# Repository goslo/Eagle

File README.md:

# Eagle
 A bunch of PCB designs

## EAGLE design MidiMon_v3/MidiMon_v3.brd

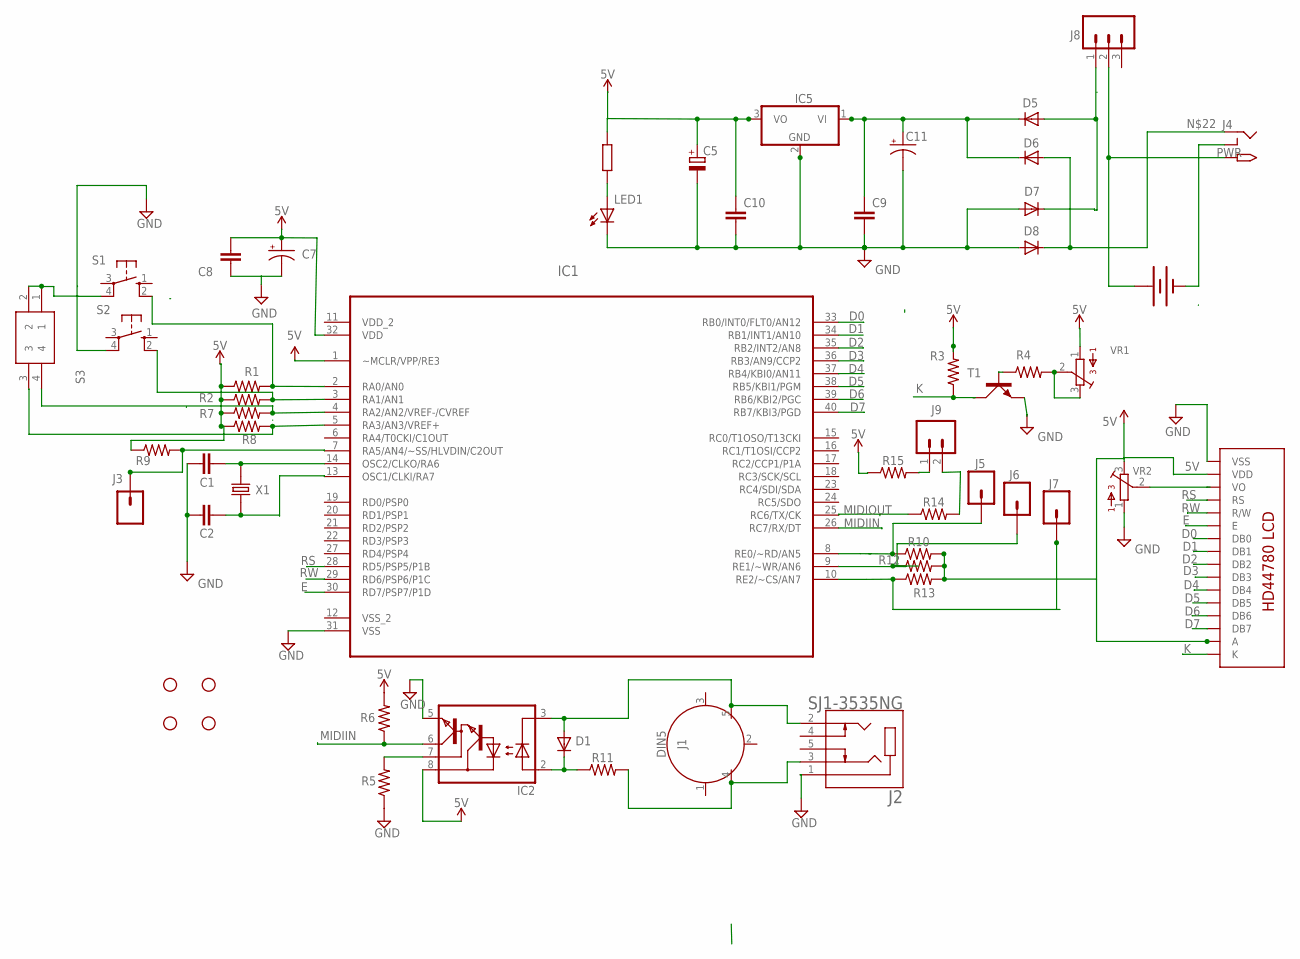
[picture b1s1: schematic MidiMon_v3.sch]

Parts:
BAT1: BATTERY; PP3_BATTERBOX
C1, C2: 33pF; CAP-PTH-2.54
C5: 10uf; E2,5-7
C7: 10uF; CPOL-RADIAL-2.5MM-5MM
C8: 0.1uF; C025-024X044
C9: 330nf; C025-024X044
C10: 100nf; C025-024X044
C11: 2200uf; E5-10,5
D1: DIODEDO-1N4148; DO-1N4148
D5, D6, D7, D8: 1N4004; DO-VERT
H1, H2, H3, H4: STAND-OFFTIGHT; STAND-OFF-TIGHT
IC1: PIC18F4520-I/P; DIP254P1524X533-40
IC2: 6N138; DIL08
IC5: 7805TV; TO220V
J1: DIN5; DIN5-RA-PTH
J2: SJ1-3535NG; CUI_SJ1-3535NG
J3, J5, J6, J7: CONN_01; 1X01
J4: 2.1MMJACKTHM; PJ-102A
J8: CONN_03; 1X03
J9: CONN_02; 1X02
LED1: LED3MM
R1, R2, R3, R7, R8, R9, R10, R12, R13: 10k; AXIAL-0.3
R4: 1k; AXIAL-0.3
R5: 5.6k; AXIAL-0.3
R6: 1.2k; AXIAL-0.3
R11, R14, R15: 220; AXIAL-0.3
R20: 1k; 0207/7
S1, S2: 40-XX; B3F-40XX
S3: 195-2MST; DIPS774W56P254L726H790Q4N
T1: 2N3904; TO92D
U$2: LCD-HD4478020X4-3HOLES; LCD-20X4-3HOLES
VR1, VR2: BOURNS_3362P_TRIMMERP; BOURNS_3362P_TRIMMER
X1: ECS-100-18-4X; XTAL_ECS-100-18-4X

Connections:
5V: C5.+, C7.1 (+), C8.2, C10.1, IC1.1 (~MCLR/VPP/RE3), IC1.32 (VDD), IC2.8 (VCC), IC5.3 (VO), R1.P$1 (1), R2.P$1 (1), R3.P$2 (2), R6.P$2 (2), R7.P$1 (1), R8.P$1 (1), R9.P$1 (1), R10.P$2 (2), R12.P$2 (2), R13.P$2 (2), R15.P$1 (1), R20.1, U$2.P$2 (VDD), U$2.P$15 (A), VR1.1, VR2.3
D0: IC1.33 (RB0/INT0/FLT0/AN12), U$2.P$7 (DB0)
D1: IC1.34 (RB1/INT1/AN10), U$2.P$8 (DB1)
D2: IC1.35 (RB2/INT2/AN8), U$2.P$9 (DB2)
D3: IC1.36 (RB3/AN9/CCP2), U$2.P$10 (DB3)
D4: IC1.37 (RB4/KBI0/AN11), U$2.P$11 (DB4)
D5: IC1.38 (RB5/KBI1/PGM), U$2.P$12 (DB5)
D6: IC1.39 (RB6/KBI2/PGC), U$2.P$13 (DB6)
D7: IC1.40 (RB7/KBI3/PGD), U$2.P$14 (DB7)
E: IC1.30 (RD7/PSP7/P1D), U$2.P$6 (E)
GND: C1.1, C2.1, C5.-, C7.2 (-), C8.1, C9.2, C10.2, C11.-, D7.A, D8.A, IC1.31 (VSS), IC2.5 (GND), IC5.2 (GND), J2.1, LED1.K (C), R5.P$1 (1), S1.4 (P1), S2.4 (P1), S3.1, S3.2, T1.E, U$2.P$1 (VSS), VR2.1
K: R3.P$1 (1), T1.C, U$2.P$16 (K)
MIDIIN: IC1.26 (RC7/RX/DT), IC2.6 (VO), R6.P$1 (1)
unnamed: BAT1.0V (-), J4.RING_SW
unnamed: R4.P$2 (2), VR1.2, VR1.3
unnamed: IC2.7 (VB), R5.P$2 (2)
unnamed: D1.C, IC2.2 (A), R11.P$1 (1)
unnamed: J1.4, J2.3, R11.P$2 (2)
unnamed: D1.A, IC2.3 (C), J1.5, J2.2
unnamed: C1.2, IC1.14 (OSC2/CLKO/RA6), X1.2
unnamed: C2.2, IC1.13 (OSC1/CLKI/RA7), X1.1
unnamed: D5.A, D7.C, J8.1
unnamed: IC1.4 (RA2/AN2/VREF-/CVREF), R7.P$2 (2), S3.4
unnamed: IC1.2 (RA0/AN0), R1.P$2 (2), S1.2 (S1)
unnamed: IC1.3 (RA1/AN1), R2.P$2 (2), S2.2 (S1)
unnamed: IC1.5 (RA3/AN3/VREF+), R8.P$2 (2), S3.3
unnamed: LED1.A, R20.2
unnamed: IC1.7 (RA5/AN4/~SS/HLVDIN/C2OUT), J3.1, R9.P$2 (2)
unnamed: IC1.25 (RC6/TX/CK), R14.P$1 (1)
unnamed: D6.A, D8.C, J4.RING
unnamed: U$2.P$3 (VO), VR2.2
unnamed: R4.P$1 (1), T1.B
unnamed: IC1.9 (RE1/~WR/AN6), J6.1, R12.P$1 (1)
unnamed: IC1.8 (RE0/~RD/AN5), J5.1, R10.P$1 (1)
unnamed: IC1.10 (RE2/~CS/AN7), J7.1, R13.P$1 (1)
unnamed: J9.2, R14.P$2 (2)
unnamed: J9.1, R15.P$2 (2)
PWR: BAT1.9V (+), J4.TIP, J8.2
RS: IC1.28 (RD5/PSP5/P1B), U$2.P$4 (RS)
RW: IC1.29 (RD6/PSP6/P1C), U$2.P$5 (R/W)
VDD_2: IC1.11 (VDD_2)
VIN: C9.1, C11.+, D5.C, D6.C, IC5.1 (VI)
VSS_2: IC1.12 (VSS_2)

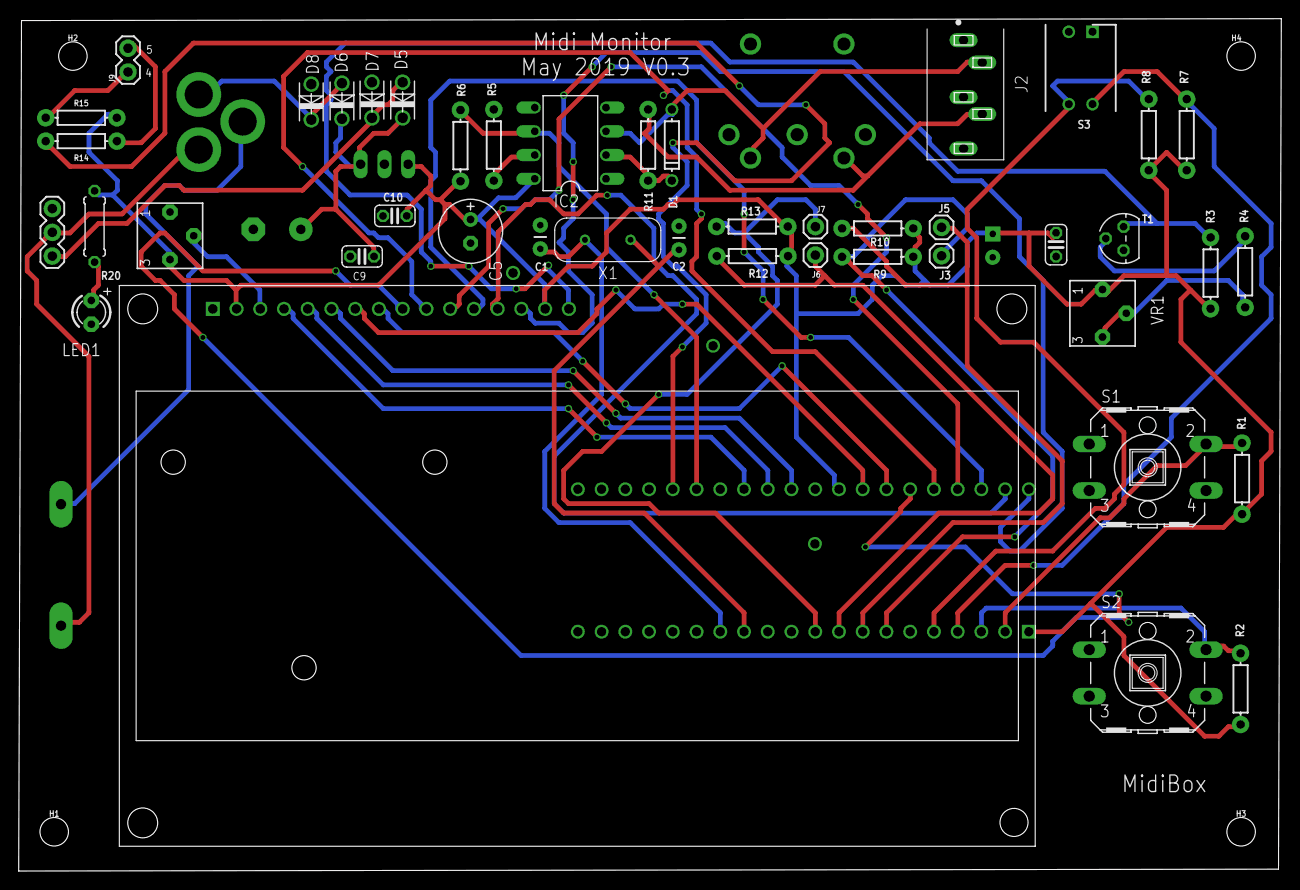
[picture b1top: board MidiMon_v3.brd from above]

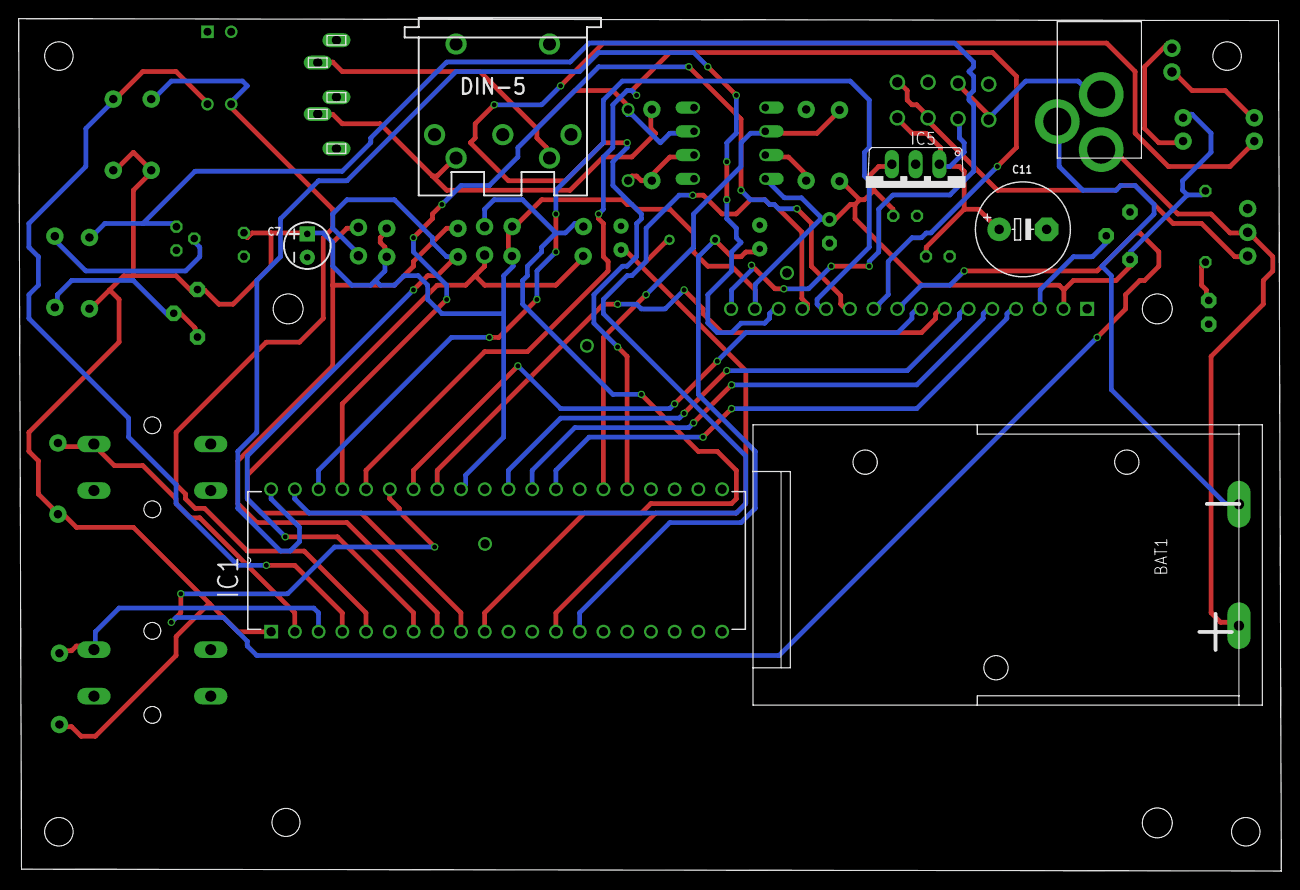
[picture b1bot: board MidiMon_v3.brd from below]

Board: 2 copper layers, 135.1 x 91.2 mm, 55 parts (7 on the bottom side), 41 nets.

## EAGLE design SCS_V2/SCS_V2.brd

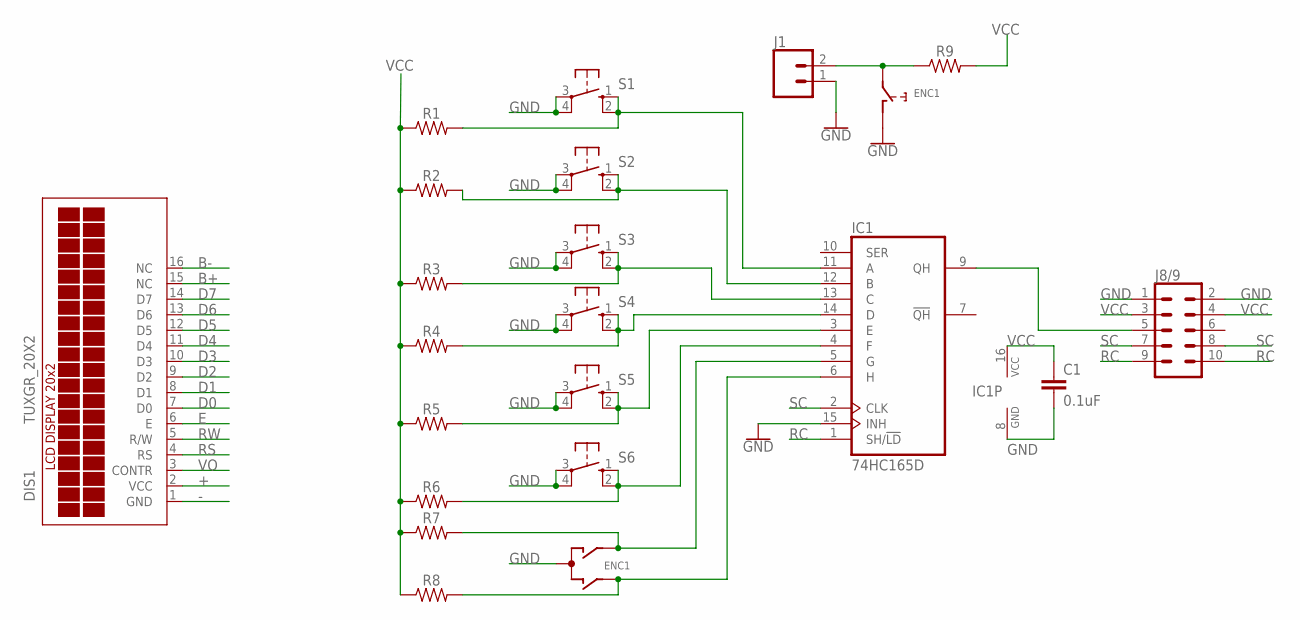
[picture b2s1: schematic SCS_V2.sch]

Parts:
C1: 0.1uF; 0603
DIS1: TUXGR_20X2
ENC1: EC12E_SW; ALPS_EC12E_SW
IC1: 74HC165D; SO16
J1: CONN_02; 1X02
J8/9: CONN_05X2SHD_LOCK; 2X5-SHROUDED_LOCK
R1, R2, R3, R4, R5, R6, R7, R8, R9: 10k; 0603
S1, S2, S3, S4, S5, S6: 40-XX; B3F-40XX

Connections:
+: DIS1.2 (VCC)
-: DIS1.1 (GND)
B+: DIS1.15 (NC)
B-: DIS1.16 (NC)
D0: DIS1.7 (D0)
D1: DIS1.8 (D1)
D2: DIS1.9 (D2)
D3: DIS1.10 (D3)
D4: DIS1.11 (D4)
D5: DIS1.12 (D5)
D6: DIS1.13 (D6)
D7: DIS1.14 (D7)
E: DIS1.6 (E)
GND: C1.2, ENC1.C, ENC1.D (1), IC1.8 (GND), IC1.15 (INH), J1.1, J8/9.1, J8/9.2, S1.3, S1.4 (P1), S2.3, S2.4 (P1), S3.3, S3.4 (P1), S4.3, S4.4 (P1), S5.3, S5.4 (P1), S6.3, S6.4 (P1)
unnamed: IC1.3 (E), R5.2, S5.1 (S), S5.2 (S1)
unnamed: ENC1.A, IC1.5 (G), R7.2
unnamed: IC1.4 (F), R6.2, S6.1 (S), S6.2 (S1)
unnamed: IC1.9 (QH), J8/9.5
unnamed: IC1.14 (D), R4.2, S4.1 (S), S4.2 (S1)
unnamed: IC1.13 (C), R3.2, S3.1 (S), S3.2 (S1)
unnamed: IC1.12 (B), R2.2, S2.1 (S), S2.2 (S1)
unnamed: IC1.11 (A), R1.2, S1.1 (S), S1.2 (S1)
unnamed: ENC1.B, IC1.6 (H), R8.2
unnamed: ENC1.E (2), J1.2, R9.1
RC: IC1.1 (SH/!LD), J8/9.9, J8/9.10
RS: DIS1.4 (RS)
RW: DIS1.5 (R/W)
SC: IC1.2 (CLK), J8/9.7, J8/9.8
VCC: C1.1, IC1.16 (VCC), J8/9.3, J8/9.4, R1.1, R2.1, R3.1, R4.1, R5.1, R6.1, R7.1, R8.1, R9.2
VO: DIS1.3 (CONTR)

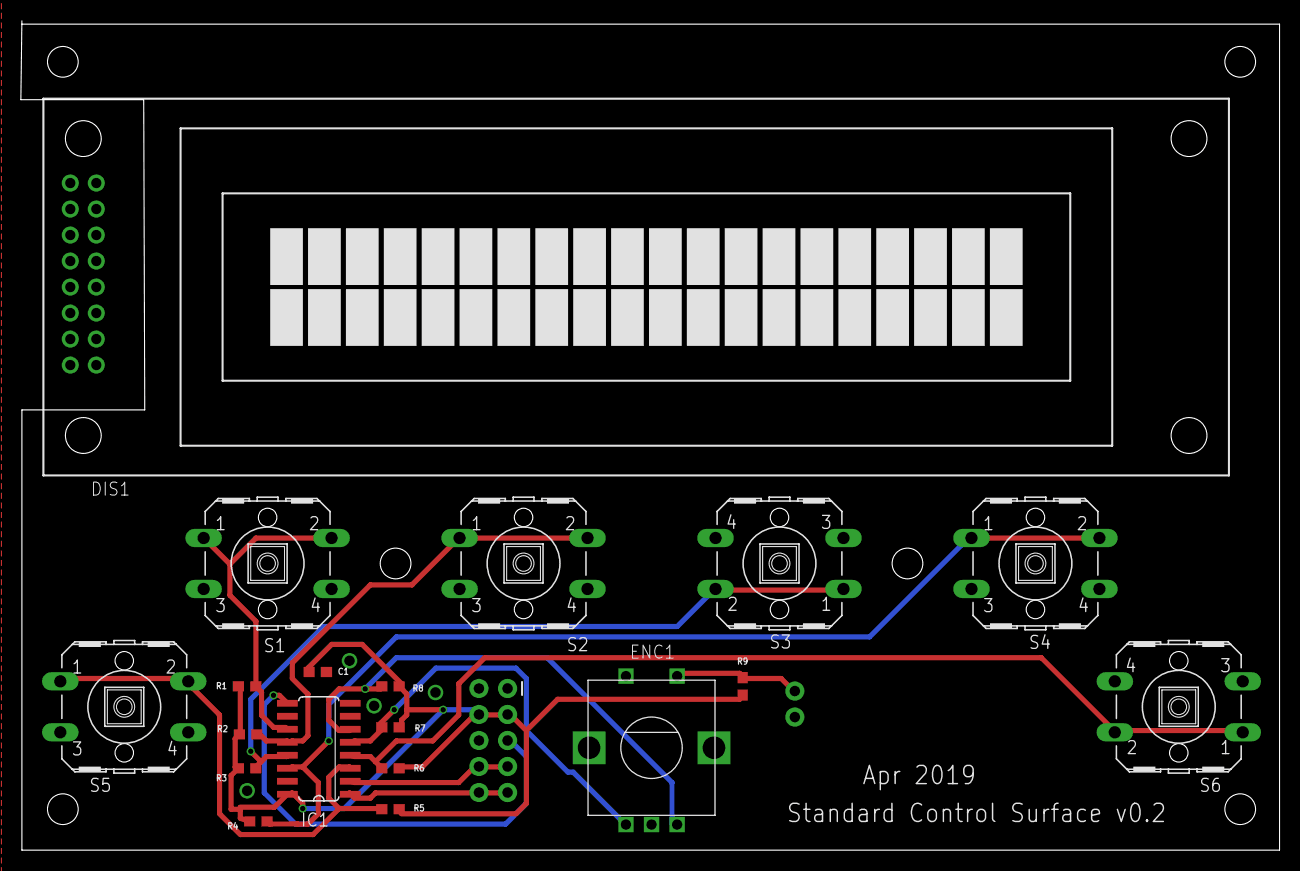
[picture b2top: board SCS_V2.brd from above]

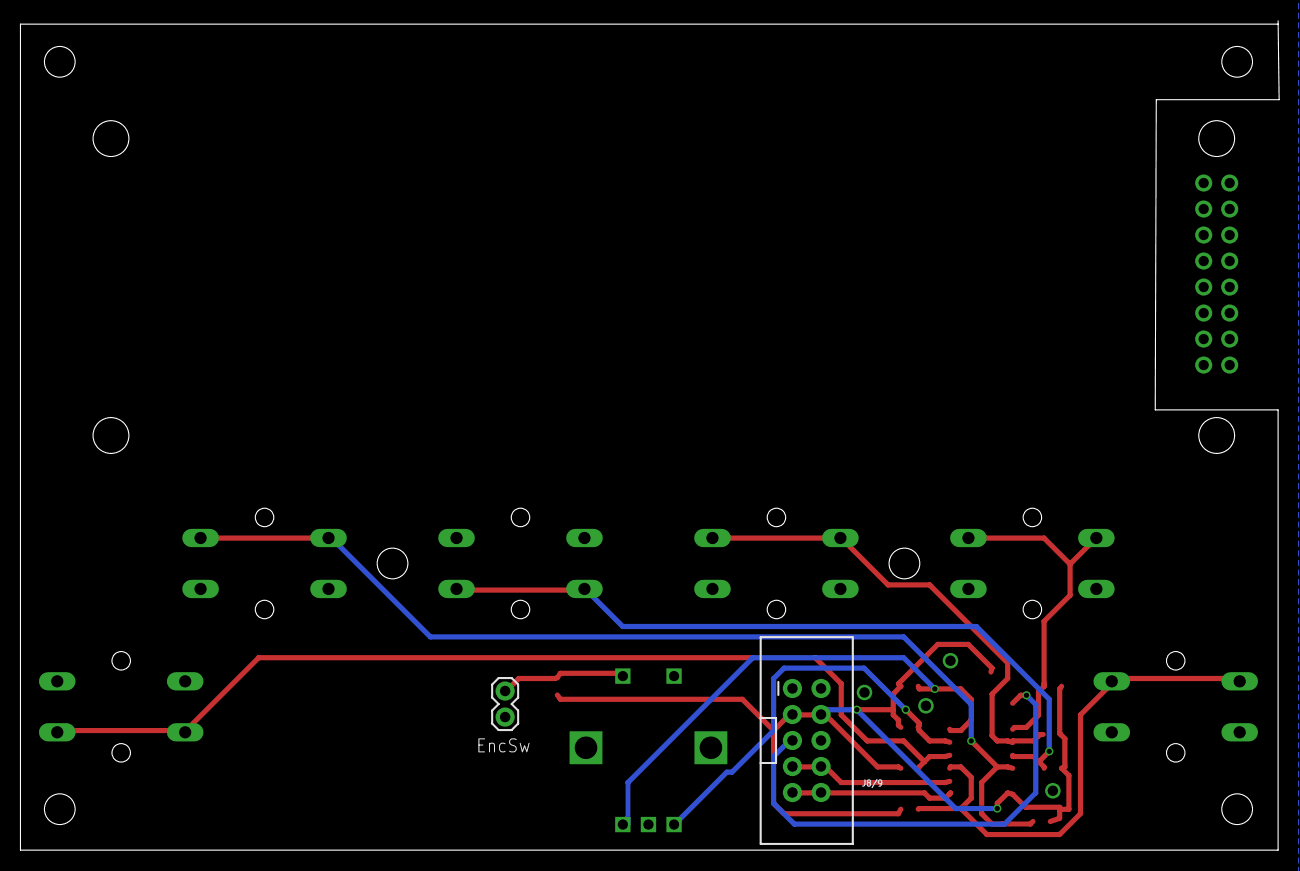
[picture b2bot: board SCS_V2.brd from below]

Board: 2 copper layers, 122.9 x 81.0 mm, 21 parts (2 on the bottom side), 14 nets.

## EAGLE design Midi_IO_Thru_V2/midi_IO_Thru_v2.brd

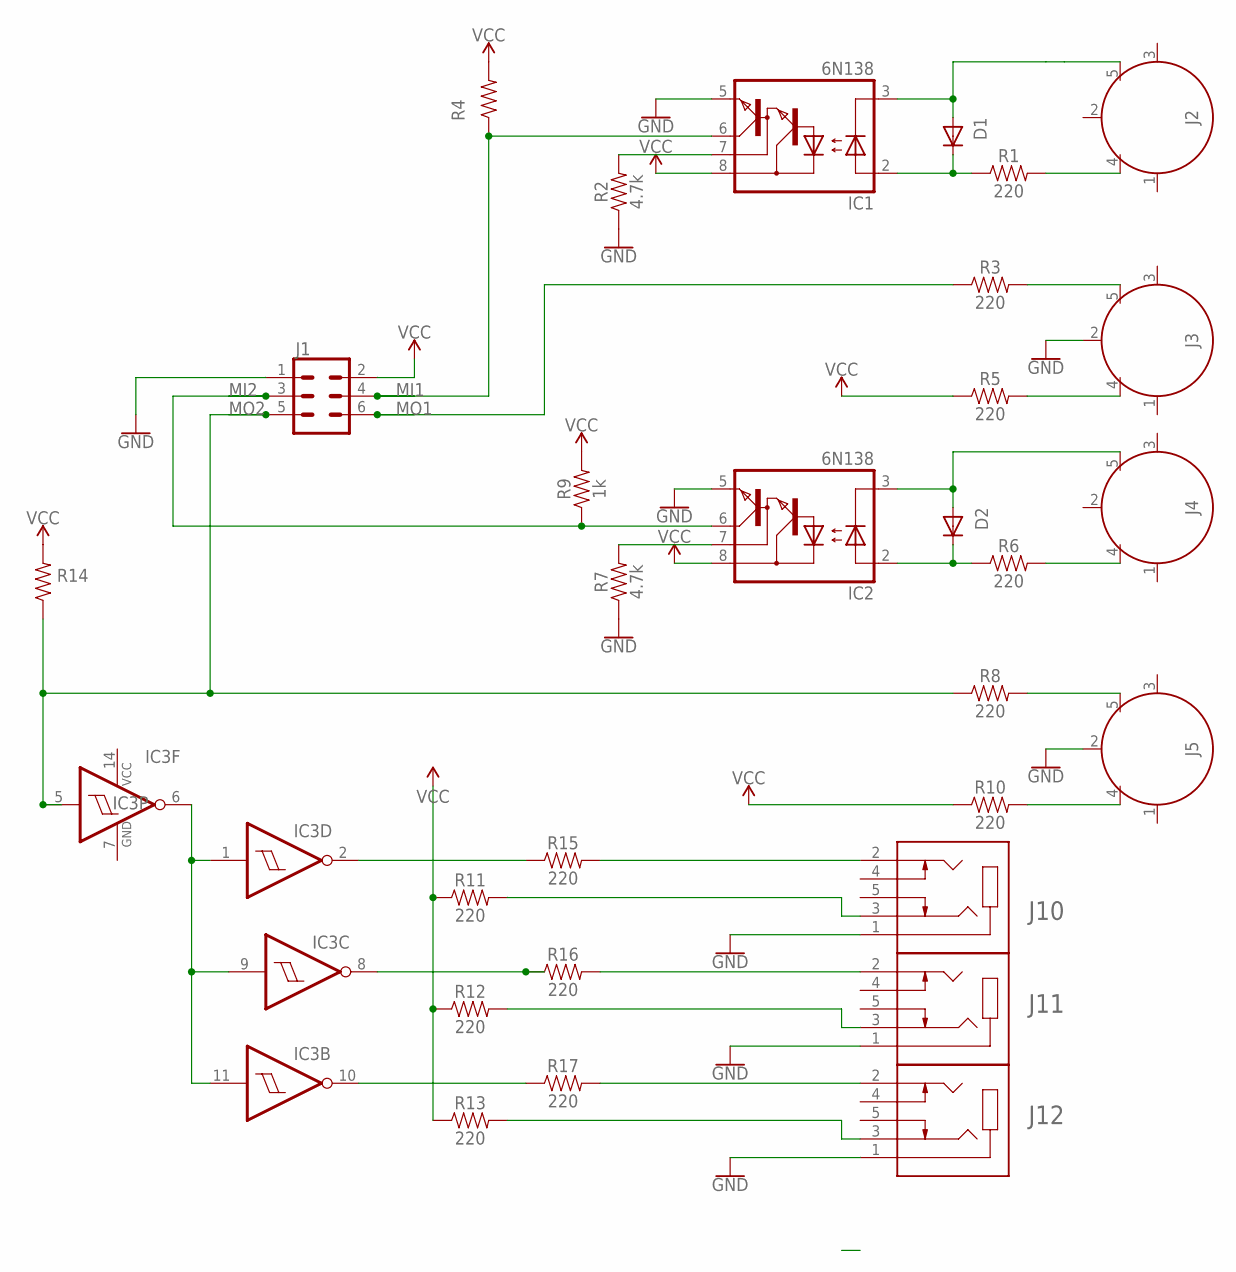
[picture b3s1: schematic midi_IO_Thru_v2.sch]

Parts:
D1, D2: 1N4148DO35-7; DO35-7
IC1, IC2: 6N138; DIL08
IC3: 74HC14D; SO14
J1: CONN_03X2SHROUD; 2X3-SHROUDED
J2, J3, J4, J5: DIN5; DIN5-RA-PTH
J10, J11, J12: SJ1-3535NG; CUI_SJ1-3535NG
R1, R3, R5, R6, R8, R10, R11, R12, R13, R15, R16, R17: 220; AXIAL-0.3
R2, R7: 4.7k; AXIAL-0.3
R4, R9: 1k; AXIAL-0.3
R14: 10k; AXIAL-0.3

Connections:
GND: IC1.5 (GND), IC2.5 (GND), IC3.7 (GND), J1.1, J3.2, J5.2, J10.1, J11.1, J12.1, R2.P$1 (1), R7.P$1 (1)
MI1: IC1.6 (VO), J1.4, R4.P$1 (1)
MI2: IC2.6 (VO), J1.3, R9.P$1 (1)
MO1: J1.6, R3.P$1 (1)
MO2: IC3.5 (I), J1.5, R8.P$1 (1), R14.P$1 (1)
unnamed: IC3.1 (I), IC3.6 (O), IC3.9 (I), IC3.11 (I)
unnamed: IC3.2 (O), R15.P$1 (1)
unnamed: IC3.8 (O), R16.P$1 (1)
unnamed: IC3.10 (O), R17.P$1 (1)
unnamed: J10.2, R15.P$2 (2)
unnamed: J11.2, R16.P$2 (2)
unnamed: J12.2, R17.P$2 (2)
unnamed: D1.C, IC1.2 (A), R1.P$1 (1)
unnamed: J10.3, R11.P$2 (2)
unnamed: J11.3, R12.P$2 (2)
unnamed: J12.3, R13.P$2 (2)
unnamed: J5.4, R10.P$2 (2)
unnamed: D2.A, IC2.3 (C), J4.5
unnamed: D2.C, IC2.2 (A), R6.P$1 (1)
unnamed: J4.4, R6.P$2 (2)
unnamed: J2.4, R1.P$2 (2)
unnamed: IC1.7 (VB), R2.P$2 (2)
unnamed: J3.5, R3.P$2 (2)
unnamed: J3.4, R5.P$2 (2)
unnamed: J5.5, R8.P$2 (2)
unnamed: IC2.7 (VB), R7.P$2 (2)
unnamed: D1.A, IC1.3 (C), J2.5
VCC: IC1.8 (VCC), IC2.8 (VCC), IC3.14 (VCC), J1.2, R4.P$2 (2), R5.P$1 (1), R9.P$2 (2), R10.P$1 (1), R11.P$1 (1), R12.P$1 (1), R13.P$1 (1), R14.P$2 (2)

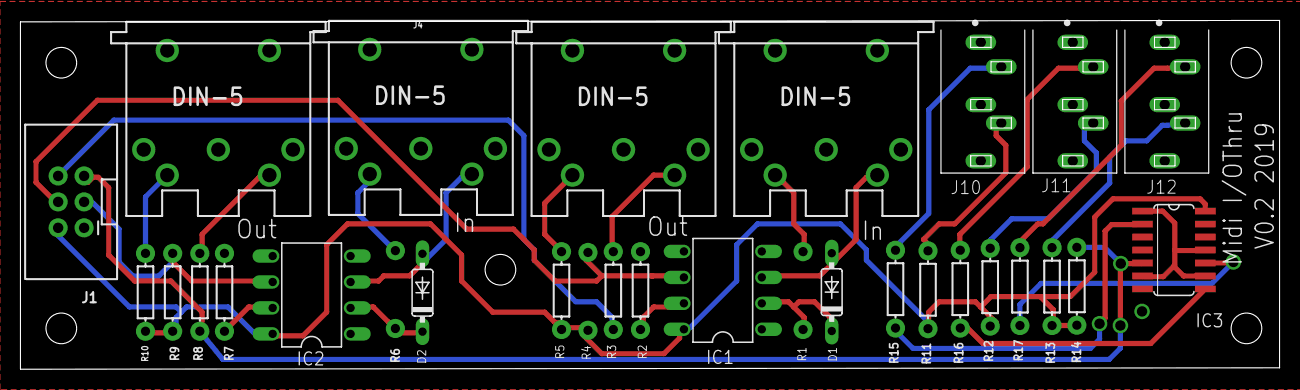
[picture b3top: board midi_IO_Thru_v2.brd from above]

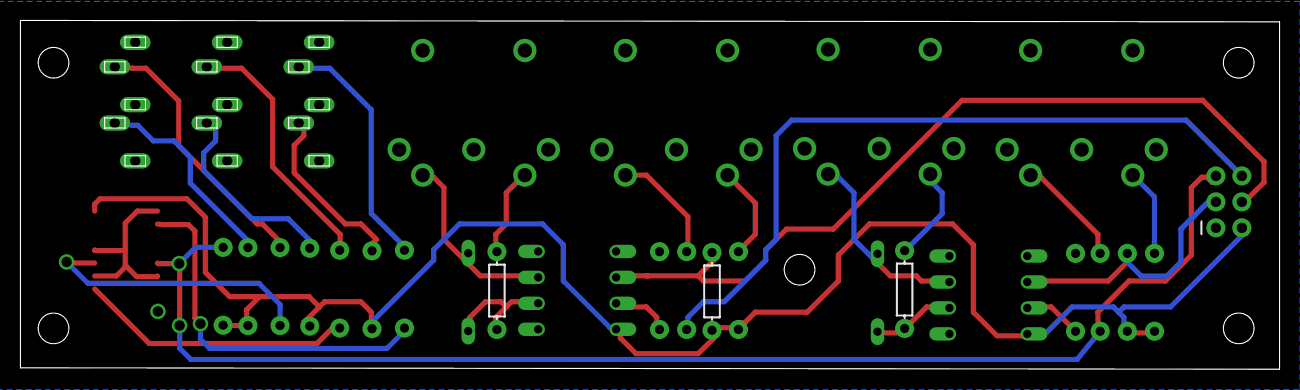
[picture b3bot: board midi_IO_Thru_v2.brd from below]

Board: 2 copper layers, 123.2 x 34.1 mm, 30 parts (3 on the bottom side), 28 nets.

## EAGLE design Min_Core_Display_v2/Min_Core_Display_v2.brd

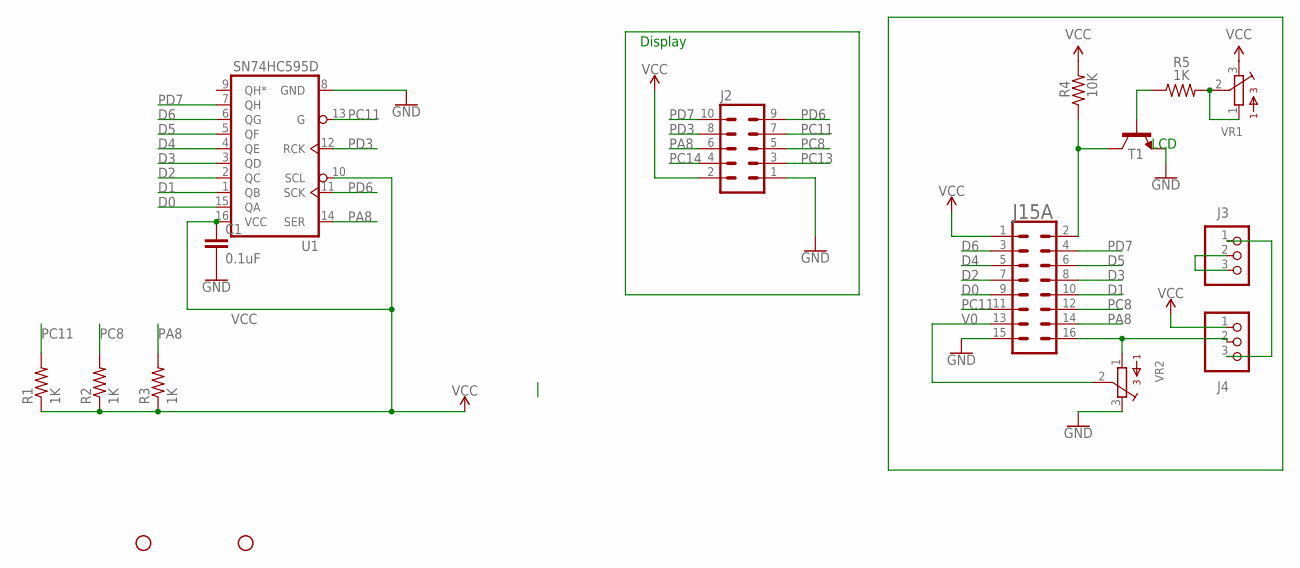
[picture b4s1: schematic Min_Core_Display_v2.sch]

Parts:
C1: 0.1uF; 0603
H2, H4: STAND-OFFTIGHT; STAND-OFF-TIGHT
J2: 10PIN_BACKSIDE
J3, J4: PINHD-1X3; 1X03
J15A: CONN_08X2_SHROUD; 2X8-SHROUDED_LOCK
R1, R2, R3, R5: 1K; R0603
R4: 10K; R0603
T1: 600mA/40V; TO-92
U1: SN74HC595D; SO16
VR1, VR2: BOURNS_3362P_TRIMMERP; BOURNS_3362P_TRIMMER

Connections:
D0: J15A.9, U1.15 (QA)
D1: J15A.10, U1.1 (QB)
D2: J15A.7, U1.2 (QC)
D3: J15A.8, U1.3 (QD)
D4: J15A.5, U1.4 (QE)
D5: J15A.6, U1.5 (QF)
D6: J15A.3, U1.6 (QG)
GND: C1.2, J2.1, J15A.15, T1.3 (E), U1.8 (GND), VR2.3
unnamed: R5.1, T1.2 (B)
unnamed: J3.2, J3.3
unnamed: R5.2, VR1.1, VR1.2
unnamed: J15A.2, R4.1, T1.1 (C)
unnamed: J3.1, J4.3
unnamed: J4.2, J15A.16, VR2.1
PA8: J2.6, J15A.14, R3.2, U1.14 (SER)
PC8: J2.5, J15A.12, R2.2
PC11: J2.7, J15A.11, R1.2, U1.13 (G)
PC13: J2.3
PC14: J2.4
PD3: J2.8, U1.12 (RCK)
PD6: J2.9, U1.11 (SCK)
PD7: J2.10, J15A.4, U1.7 (QH)
V0: J15A.13, VR2.2
VCC: C1.1, J2.2, J4.1, J15A.1, R1.1, R2.1, R3.1, R4.2, U1.10 (SCL), U1.16 (VCC), VR1.3

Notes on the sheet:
Display
LCD

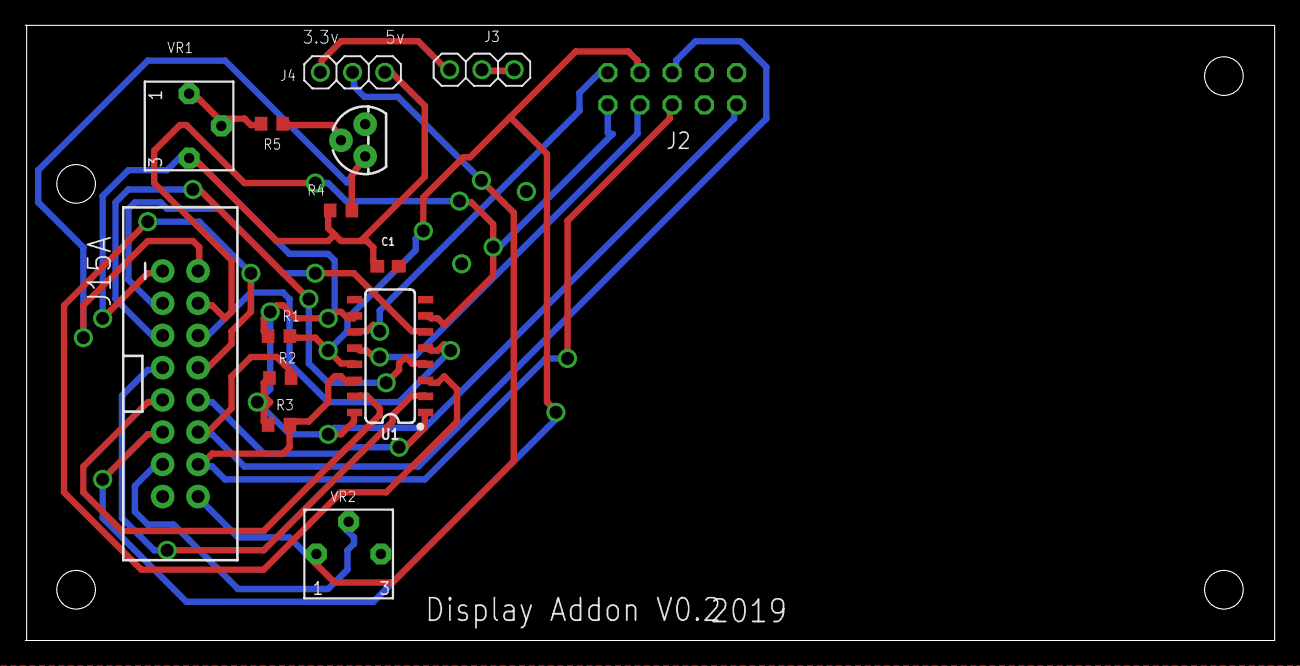
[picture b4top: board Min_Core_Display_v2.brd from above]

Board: 2 copper layers, 98.5 x 48.5 mm, 18 parts (0 on the bottom side), 22 nets.

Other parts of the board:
H1, H3: STAND-OFFTIGHT; STAND-OFF-TIGHT

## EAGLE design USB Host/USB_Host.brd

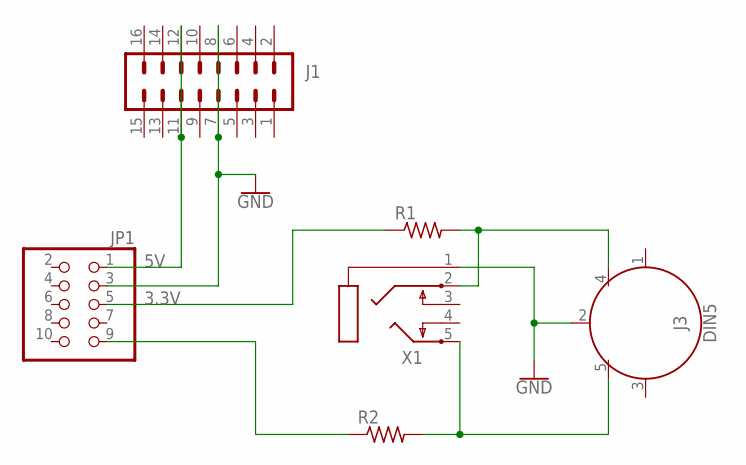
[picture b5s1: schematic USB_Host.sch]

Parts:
J1: CONN_08X2_SHROUD; 2X8-SHROUDED_LOCK
J3: DIN5; DIN5-RA-PTH
JP1: PINHD-2X5; 2X05
R1, R2: 68; 0204/7
X1: PG203J

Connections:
3.3V: JP1.5, R1.1
5V: J1.11, J1.12, JP1.1
GND: J1.7, J1.8, J3.2, JP1.3, X1.1
unnamed: JP1.9, R2.1
unnamed: J3.4, R1.2, X1.2
unnamed: J3.5, R2.2, X1.5

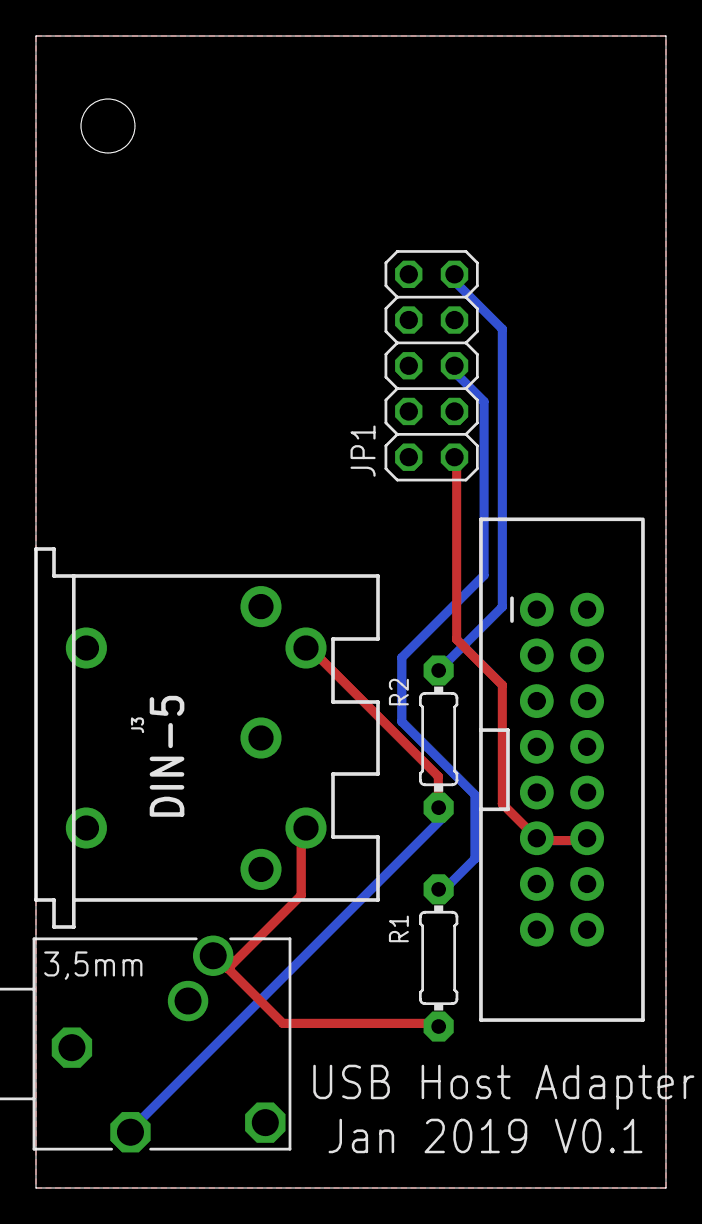
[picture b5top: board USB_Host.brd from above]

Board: 2 copper layers, 35.0 x 64.0 mm, 6 parts (0 on the bottom side), 6 nets.

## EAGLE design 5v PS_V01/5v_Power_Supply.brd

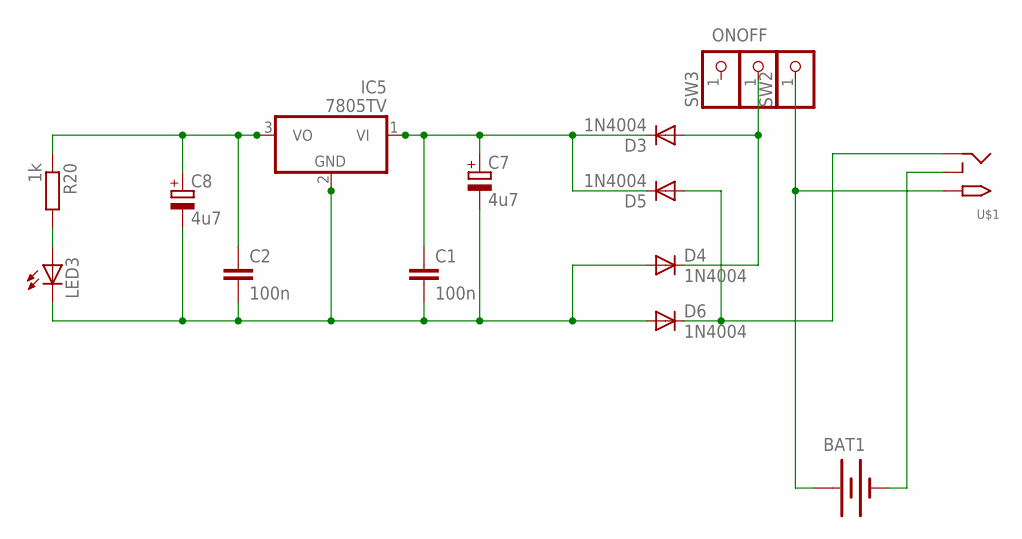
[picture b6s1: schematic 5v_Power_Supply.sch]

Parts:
BAT1: BATTERY; PP3_BATTERBOX
C1, C2: 100n; C025-024X044
C7, C8: 4u7; E2,5-7
D3, D4, D5, D6: 1N4004; DO-VERT
IC5: 7805TV; TO220V
LED3: LED3MM
ONOFF: PINHD-1X1; 1X01
R20: 1k; 0207/7
SW2, SW3: PINHD-1X1; 1X01
U$1: 2.1MMJACKTHM; PJ-102A

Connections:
unnamed: LED3.A, R20.2
unnamed: D5.A, D6.C, U$1.RING
unnamed: C2.1, C8.+, IC5.3 (VO), R20.1
unnamed: C1.2, C2.2, C7.-, C8.-, D4.A, D6.A, IC5.2 (GND), LED3.K (C)
unnamed: D3.A, D4.C, ONOFF.1
unnamed: BAT1.0V (-), U$1.RING_SW
PWR+: BAT1.9V (+), SW2.1, U$1.TIP
VIN: C1.1, C7.+, D3.C, D5.C, IC5.1 (VI)

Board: 2 copper layers, 16 parts (0 on the bottom side), 8 nets, no tracks yet.

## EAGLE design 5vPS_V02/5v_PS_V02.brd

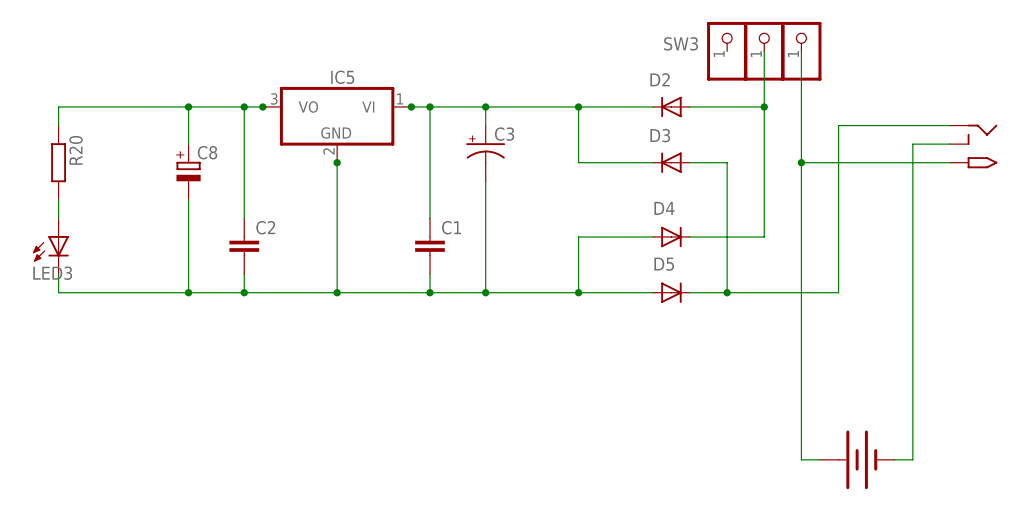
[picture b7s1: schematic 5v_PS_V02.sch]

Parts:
BAT1: BATTERY; PP3_BATTERBOX
C1: 330nf; C025-024X044
C2: 100nf; C025-024X044
C3: 2200uf; E5-10,5
C8: 10uf; E2,5-7
D2, D3, D4, D5: 1N4004; DO-VERT
IC5: 7805TV; TO220V
J1: 2.1MMJACKTHM; PJ-102A
LED3: LED3MM
ONOFF: PINHD-1X1; 1X01
R20: 1k; 0207/7
SW2, SW3: PINHD-1X1; 1X01

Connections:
unnamed: LED3.A, R20.2
unnamed: D3.A, D5.C, J1.RING
unnamed: C2.1, C8.+, IC5.3 (VO), R20.1
unnamed: C1.2, C2.2, C3.-, C8.-, D4.A, D5.A, IC5.2 (GND), LED3.K (C)
unnamed: D2.A, D4.C, ONOFF.1
unnamed: BAT1.0V (-), J1.RING_SW
PWR+: BAT1.9V (+), J1.TIP, SW2.1
VIN: C1.1, C3.+, D2.C, D3.C, IC5.1 (VI)

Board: 2 copper layers, 16 parts (0 on the bottom side), 8 nets, no tracks yet.

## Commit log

2019-01-27 First commit Signed-off-by: goslo <digit99@mailinator.com>
2019-01-27 Updated PCB text Signed-off-by: goslo <digit99@mailinator.com>
2019-01-27 Adjustment Signed-off-by: goslo <digit99@mailinator.com>
2019-01-31 Adjustments to PCB Signed-off-by: goslo <digit99@mailinator.com>
2019-01-31 Adjusted again Signed-off-by: goslo <digit99@mailinator.com>
2019-02-01 Adjustments made Signed-off-by: goslo <digit99@mailinator.com>
2019-02-02 New Power Sw Signed-off-by: goslo <digit99@mailinator.com>
2019-02-12 More adjustments Signed-off-by: goslo <digit99@mailinator.com>
2019-04-05 More changes

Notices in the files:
parts and their libraries:
SparkFun-Capacitors: Licensing: Creative Commons ShareAlike 4.0 International - https://creativecommons.org/licenses/by-sa/4.0
